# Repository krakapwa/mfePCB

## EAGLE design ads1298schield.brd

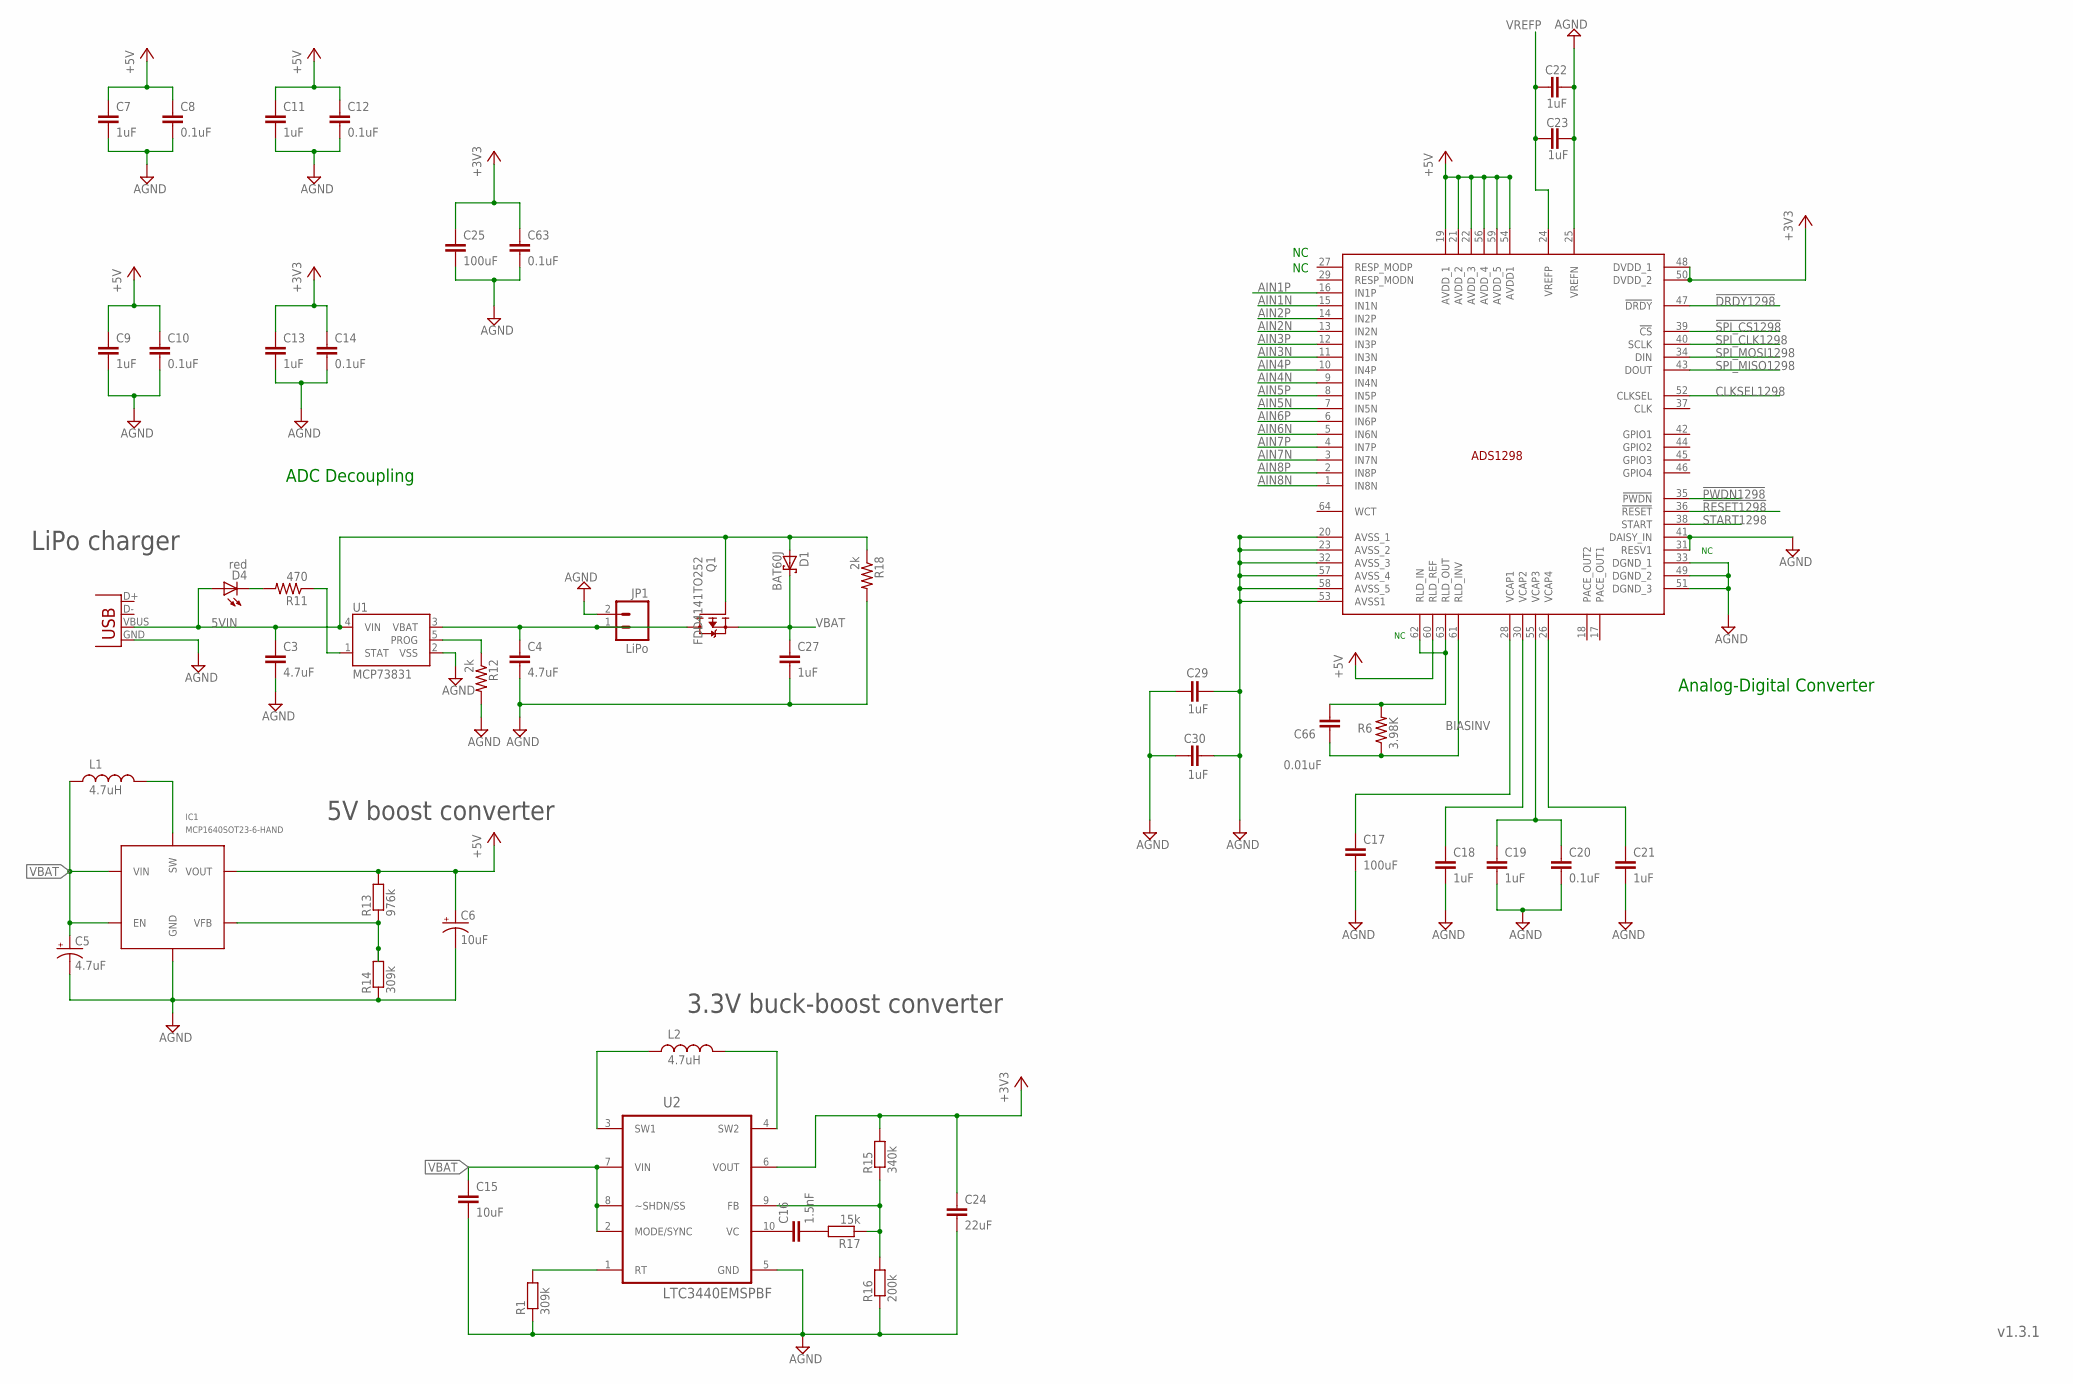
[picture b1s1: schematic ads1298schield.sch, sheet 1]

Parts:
C3, C4: 4.7uF; 0402-CAP
C5: 4.7uF; EIA3216
C6: 10uF; EIA3216
C7, C9, C11, C13, C18, C19, C21, C22, C23, C29, C30: 1uF; 0603-CAP
C8, C10, C12, C14, C20, C63: 0.1uF; 0603-CAP
C15: 10uF; 1210
C16: 1.5nF; 1210
C17, C25: 100uF; 1210
C24: 22uF; 1210
C27: 1uF; 0402-CAP
C66: 0.01uF; 0603-CAP
D1: BAT60J; SOD323_ST
D4: red; LED-0603
IC1: MCP1640SOT23-6-HAND; SOT23-6-HAND
JP1: LiPo; JST-2-SMD
L1, L2: 4.7uH; 1210-HAND
Q1: FDD4141TO252; TO252
R1, R14: 309k; 1206-HAND
R6: 3.98K; 0603-RES
R11: 470; 0402-RES
R12, R18: 2k; 0402-RES
R13: 976k; 1206-HAND
R15: 340k; 1206-HAND
R16: 200k; 1206-HAND
R17: 15k; 1206-HAND
U1: MCP73831; SOT23-5
U2: LTC3440EMSPBF; SOP50P490X110-10N
U$2: ADS1298*PAG*; TQFP64
X2: USB-MICROB

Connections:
5VIN: C3.1, D1.A, D4.A, Q1.1 (G), R18.1, U1.4 (VIN), X2.VBUS
!DRDY1298: U$2.47 (!DRDY); also elsewhere on the board
!PWDN1298: U$2.35 (!PWDN); also elsewhere on the board
!RESET1298: U$2.36 (!RESET); also elsewhere on the board
!SPI_CS1298: U$2.39 (!CS); also elsewhere on the board
+3V3: C13.1, C14.1, C24.1, C25.1, C63.1, R15.2, U2.6 (VOUT), U$2.48 (DVDD_1), U$2.50 (DVDD_2); also elsewhere on the board
+5V: C6.A (+), C7.1, C8.1, C9.1, C10.1, C11.1, C12.1, IC1.5 (VOUT), R13.2, U$2.19 (AVDD_1), U$2.21 (AVDD_2), U$2.22 (AVDD_3), U$2.54 (AVDD1), U$2.56 (AVDD_4), U$2.59 (AVDD_5), U$2.60 (RLD_REF); also elsewhere on the board
AGND: C3.2, C4.2, C5.C (-), C6.C (-), C7.2, C8.2, C9.2, C10.2, C11.2, C12.2, C13.2, C14.2, C15.2, C17.2, C18.2, C19.2, C20.2, C21.2, C22.2, C23.2, C24.2, C25.2, C27.2, C29.1, C29.2, C30.1, C30.2, C63.2, IC1.2 (GND), JP1.2, R1.1, R12.2, R14.1, R16.1, R18.2, U1.2 (VSS), U2.5 (GND), U$2.20 (AVSS_1), U$2.23 (AVSS_2), U$2.25 (VREFN), U$2.31 (RESV1), U$2.32 (AVSS_3), U$2.33 (DGND_1), U$2.41 (DAISY_IN), U$2.49 (DGND_2), U$2.51 (DGND_3), U$2.53 (AVSS1), U$2.57 (AVSS_4), U$2.58 (AVSS_5), X2.GND; also elsewhere on the board
AIN1N: U$2.15 (IN1N); also elsewhere on the board
AIN1P: U$2.16 (IN1P); also elsewhere on the board
AIN2N: U$2.13 (IN2N); also elsewhere on the board
AIN2P: U$2.14 (IN2P); also elsewhere on the board
AIN3N: U$2.11 (IN3N); also elsewhere on the board
AIN3P: U$2.12 (IN3P); also elsewhere on the board
AIN4N: U$2.9 (IN4N); also elsewhere on the board
AIN4P: U$2.10 (IN4P); also elsewhere on the board
AIN5N: U$2.7 (IN5N); also elsewhere on the board
AIN5P: U$2.8 (IN5P); also elsewhere on the board
AIN6N: U$2.5 (IN6N); also elsewhere on the board
AIN6P: U$2.6 (IN6P); also elsewhere on the board
AIN7N: U$2.3 (IN7N); also elsewhere on the board
AIN7P: U$2.4 (IN7P); also elsewhere on the board
AIN8N: U$2.1 (IN8N); also elsewhere on the board
AIN8P: U$2.2 (IN8P); also elsewhere on the board
BIASINV: C66.2, R6.1, U$2.61 (RLD_INV); also elsewhere on the board
CLKSEL1298: U$2.52 (CLKSEL); also elsewhere on the board
unnamed: C17.1, U$2.28 (VCAP1)
unnamed: C18.1, U$2.30 (VCAP2)
unnamed: C66.1, R6.2, U$2.62 (RLD_IN), U$2.63 (RLD_OUT)
unnamed: C21.1, U$2.26 (VCAP4)
unnamed: C19.1, C20.1, U$2.55 (VCAP3)
unnamed: R12.1, U1.5 (PROG)
unnamed: R11.1, U1.1 (STAT)
unnamed: R1.2, U2.1 (RT)
unnamed: D4.C, R11.2
unnamed: IC1.1 (SW), L1.2
unnamed: C5.A (+), IC1.3 (EN), IC1.6 (VIN), L1.1
unnamed: C16.1, U2.10 (VC)
unnamed: IC1.4 (VFB), R13.1, R14.2
unnamed: C15.1, U2.2 (MODE/SYNC), U2.7 (VIN), U2.8 (~SHDN/SS)
unnamed: L2.1, U2.3 (SW1)
unnamed: L2.2, U2.4 (SW2)
unnamed: R15.1, R16.2, R17.1, U2.9 (FB)
unnamed: C16.2, R17.2
SPI_CLK1298: U$2.40 (SCLK); also elsewhere on the board
SPI_MISO1298: U$2.43 (DOUT); also elsewhere on the board
SPI_MOSI1298: U$2.34 (DIN); also elsewhere on the board
START1298: U$2.38 (START); also elsewhere on the board
VBAT: C4.1, C27.1, D1.C, JP1.1, Q1.2 (S), Q1.3 (D), U1.3 (VBAT); also elsewhere on the board
VREFP: C22.1, C23.1, U$2.24 (VREFP)

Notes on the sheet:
v1.3.1
ADC Decoupling
Analog-Digital Converter
5V boost converter
LiPo charger
3.3V buck-boost converter

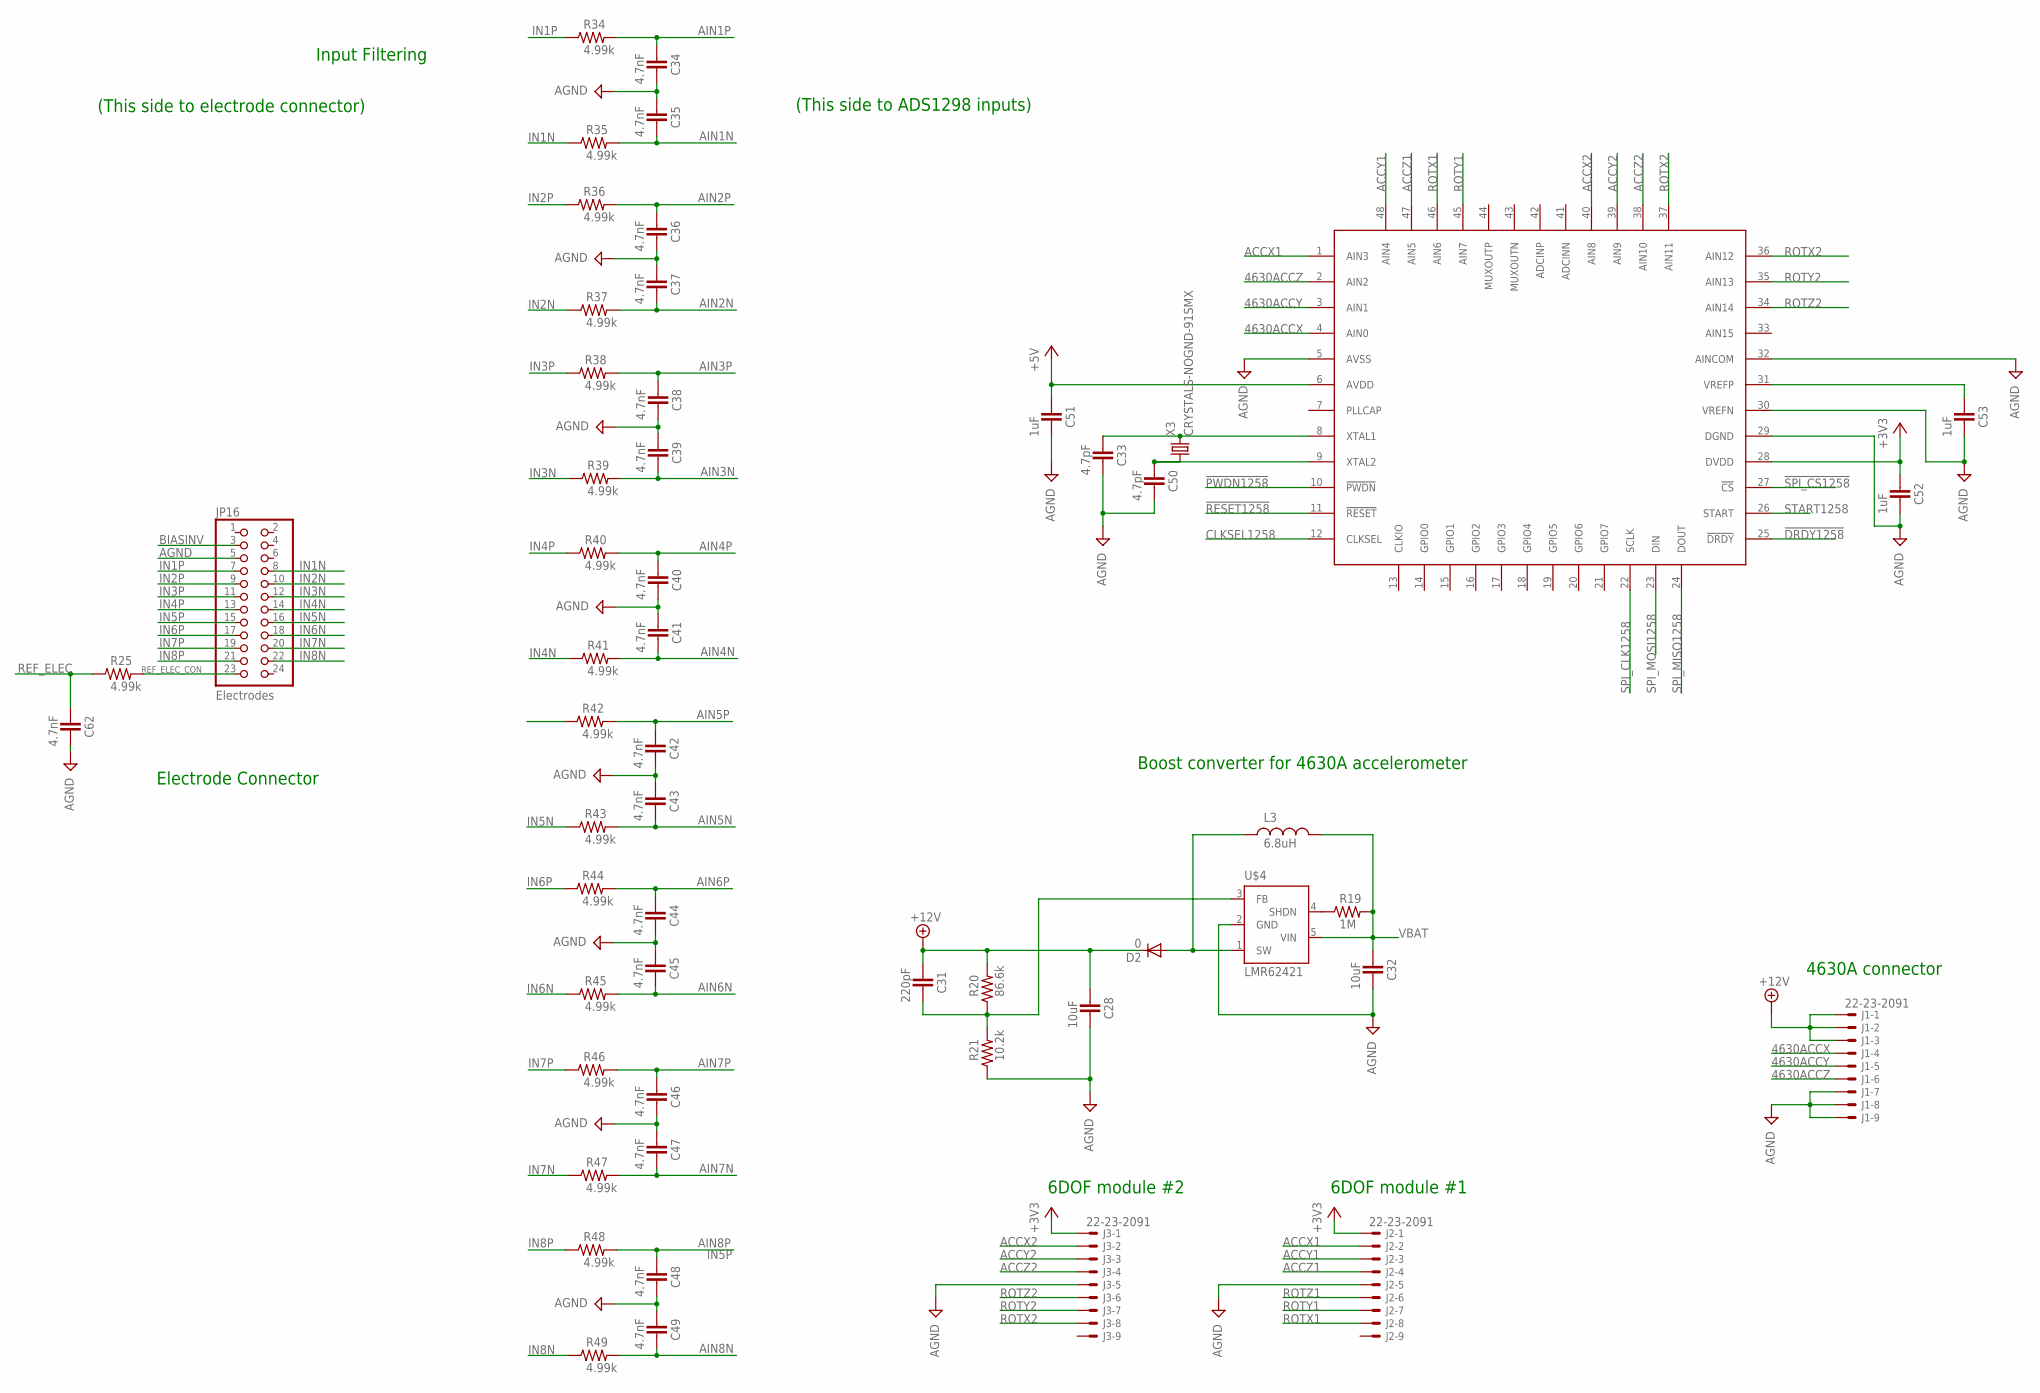
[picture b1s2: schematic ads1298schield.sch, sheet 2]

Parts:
C28, C32: 10uF; 0603-CAP
C31: 220pF; 0603-CAP
C33, C50: 4.7pF; 0603-CAP
C34, C35, C36, C37, C38, C39, C40, C41, C42, C43, C44, C45, C46, C47, C48, C49, C62: 4.7nF; 0603-CAP
C51, C52, C53: 1uF; 0603-CAP
D2: 0; MELF-MLL41
IC2: ADS1258; P-HVQFN48-7X7
J1, J2, J3: 22-23-2091
JP16: Electrodes; 2X12
L3: 6.8uH; 1210-HAND
R19: 1M; 0603-RES
R20: 86.6k; 0603-RES
R21: 10.2k; 0603-RES
R25, R34, R35, R36, R37, R38, R39, R40, R41, R42, R43, R44, R45, R46, R47, R48, R49: 4.99k; 0603-RES
U$4: LMR62421; SOT23-5
X3: CRYSTALS-NOGND-91SMX; 91SMX

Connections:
4630ACCX: IC2.4 (AIN0), J1.4
4630ACCY: IC2.3 (AIN1), J1.5
4630ACCZ: IC2.2 (AIN2), J1.6
!DRDY1258: IC2.25 (!DRDY); also elsewhere on the board
!PWDN1258: IC2.10 (!PWDN); also elsewhere on the board
!RESET1258: IC2.11 (!RESET); also elsewhere on the board
!SPI_CS1258: IC2.27 (!CS); also elsewhere on the board
+3V3: C52.1, IC2.28 (DVDD); also elsewhere on the board
+5V: C51.1, IC2.6 (AVDD); also elsewhere on the board
+12V: C28.1, C31.1, D2.C, J1.1, J1.2, J1.3, R20.2
AGND: C28.2, C32.2, C33.2, C34.2, C35.1, C36.2, C37.1, C38.2, C39.1, C40.2, C41.1, C42.2, C43.1, C44.2, C45.1, C46.2, C47.1, C48.2, C49.1, C50.2, C51.2, C52.2, C53.2, C62.2, IC2.5 (AVSS), IC2.29 (DGND), IC2.30 (VREFN), IC2.32 (AINCOM), J1.7, J1.8, J1.9, J2.5, J3.5, JP16.5, R21.1, U$4.2 (GND); also elsewhere on the board
AIN1N: C35.2, R35.2; also elsewhere on the board
AIN1P: C34.1, R34.2; also elsewhere on the board
AIN2N: C37.2, R37.2; also elsewhere on the board
AIN2P: C36.1, R36.2; also elsewhere on the board
AIN3N: C39.2, R39.2; also elsewhere on the board
AIN3P: C38.1, R38.2; also elsewhere on the board
AIN4N: C41.2, R41.2; also elsewhere on the board
AIN4P: C40.1, R40.2; also elsewhere on the board
AIN5N: C43.2, R43.2; also elsewhere on the board
AIN5P: C42.1, R42.2; also elsewhere on the board
AIN6N: C45.2, R45.2; also elsewhere on the board
AIN6P: C44.1, R44.2; also elsewhere on the board
AIN7N: C47.2, R47.2; also elsewhere on the board
AIN7P: C46.1, R46.2; also elsewhere on the board
AIN8N: C49.2, R49.2; also elsewhere on the board
AIN8P: C48.1, R48.2; also elsewhere on the board
BIASINV: JP16.3; also elsewhere on the board
CLKSEL1258: IC2.12 (CLKSEL); also elsewhere on the board
IN1N: JP16.8, R35.1
IN1P: JP16.7, R34.1
IN2N: JP16.10, R37.1
IN2P: JP16.9, R36.1
IN3N: JP16.12, R39.1
IN3P: JP16.11, R38.1
IN4N: JP16.14, R41.1
IN4P: JP16.13, R40.1
IN5N: JP16.16, R43.1
IN5P: JP16.15, R42.1
IN6N: JP16.18, R45.1
IN6P: JP16.17, R44.1
IN7N: JP16.20, R47.1
IN7P: JP16.19, R46.1
IN8N: JP16.22, R49.1
IN8P: JP16.21, R48.1
unnamed: R19.1, U$4.4 (SHDN)
unnamed: C33.1, IC2.8 (XTAL1), X3.2
unnamed: D2.A, L3.1, U$4.1 (SW)
unnamed: C50.1, IC2.9 (XTAL2), X3.1
unnamed: C31.2, R20.1, R21.2, U$4.3 (FB)
unnamed: C53.1, IC2.31 (VREFP)
unnamed: IC2.1 (AIN3), J2.2
unnamed: IC2.48 (AIN4), J2.3
unnamed: IC2.40 (AIN8), J3.2
unnamed: IC2.39 (AIN9), J3.3
unnamed: IC2.38 (AIN10), J3.4
unnamed: IC2.34 (AIN14), J3.6
unnamed: IC2.35 (AIN13), J3.7
unnamed: IC2.36 (AIN12), IC2.37 (AIN11), J3.8
REF_ELEC: C62.1, R25.1
REF_ELEC_CON: JP16.23, R25.2
SPI_CLK1258: IC2.22 (SCLK); also elsewhere on the board
SPI_MISO1258: IC2.24 (DOUT); also elsewhere on the board
SPI_MOSI1258: IC2.23 (DIN); also elsewhere on the board
START1258: IC2.26 (START); also elsewhere on the board
VBAT: C32.1, L3.2, R19.2, U$4.5 (VIN); also elsewhere on the board

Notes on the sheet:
Electrode Connector
Input Filtering
(This side to ADS1298 inputs)
(This side to electrode connector)
Boost converter for 4630A accelerometer
4630A connector
6DOF module #1
6DOF module #2

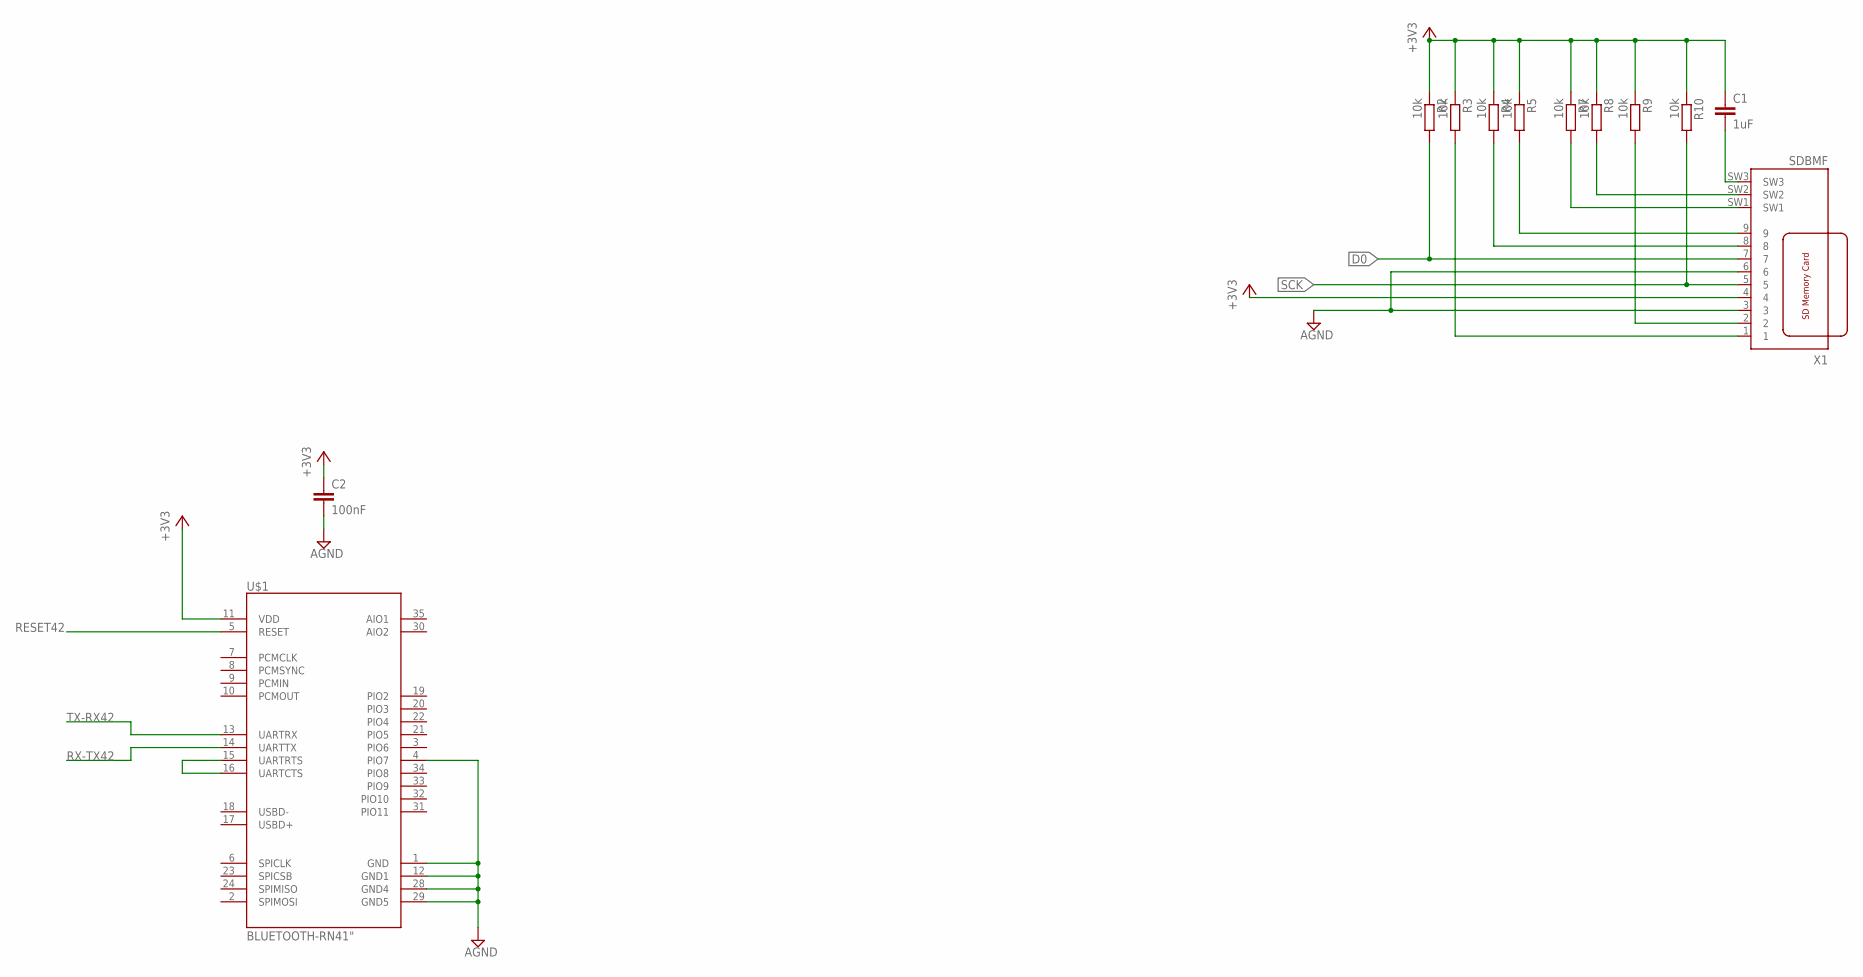
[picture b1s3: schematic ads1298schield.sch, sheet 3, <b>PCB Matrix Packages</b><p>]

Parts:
C1: 1uF; C1608
C2: 100nF; C0603
R2, R3, R4, R5, R7, R8, R9, R10: 10k; M1406
U$1: BLUETOOTH-RN41"; RN41
X1: SDBMF; SDBMF-009XXBXX2

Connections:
+3V3: C1.1, C2.1, R2.1, R3.1, R4.1, R5.1, R7.1, R8.1, R9.1, R10.1, U$1.11 (VDD), X1.4; also elsewhere on the board
AGND: C2.2, U$1.1 (GND), U$1.4 (PIO7), U$1.12 (GND1), U$1.28 (GND4), U$1.29 (GND5), X1.3, X1.6; also elsewhere on the board
CMD: R9.2, X1.2
D0: R2.2, X1.7
LINK: U$1.15 (UARTRTS), U$1.16 (UARTCTS)
unnamed: R3.2, X1.1
unnamed: R4.2, X1.8
unnamed: R5.2, X1.9
unnamed: R7.2, X1.SW1
unnamed: R8.2, X1.SW2
unnamed: C1.2, X1.SW3
RESET42: U$1.5 (RESET); also elsewhere on the board
RX-TX42: U$1.14 (UARTTX); also elsewhere on the board
SCK: R10.2, X1.5
TX-RX42: U$1.13 (UARTRX); also elsewhere on the board

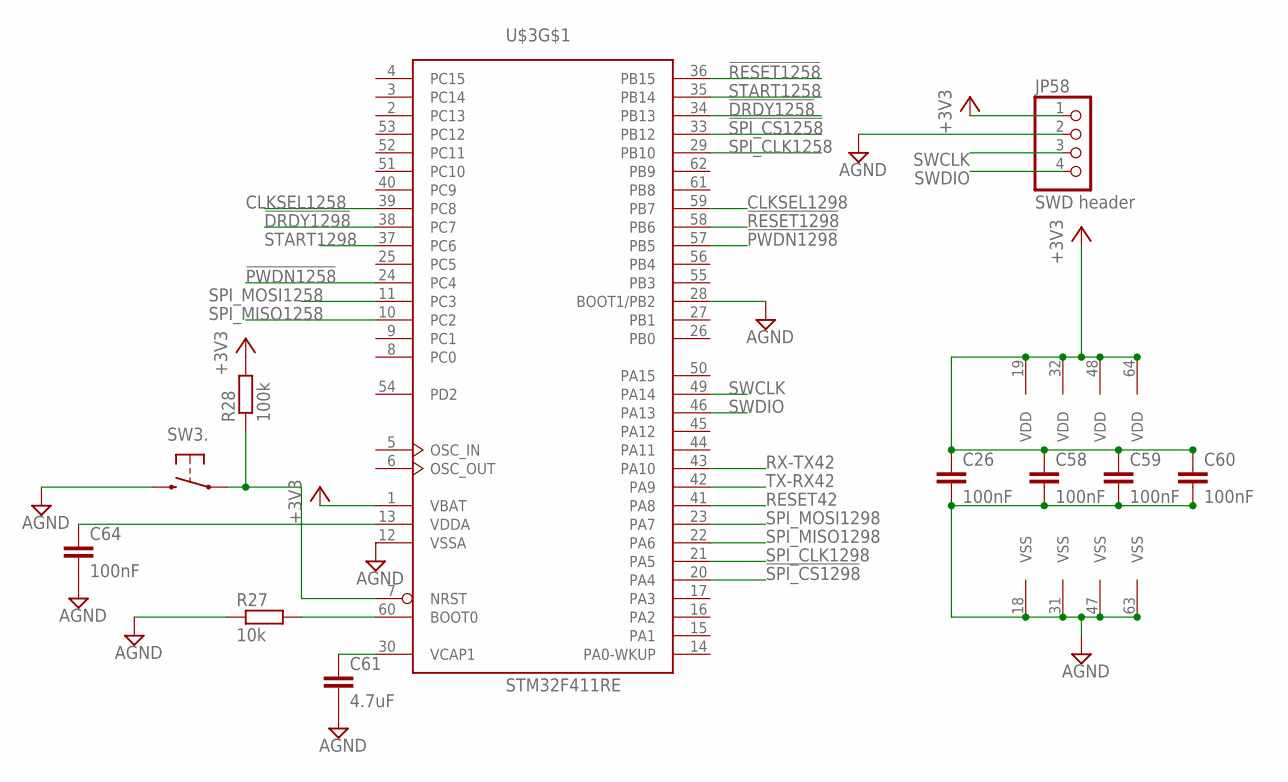
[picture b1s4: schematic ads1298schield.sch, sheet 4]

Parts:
C26, C58, C59, C60, C64: 100nF; C1210
C61: 4.7uF; C1210
JP58: SWD header; 1X04
R27: 10k; M1406
R28: 100k; M1406
SW3: !RST; SWITCH-TACT-B3U-1100P-B
U$3: STM32F411RE; LQFP64

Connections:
!DRDY1258: U$3.34 (PB13); also elsewhere on the board
!DRDY1298: U$3.38 (PC7); also elsewhere on the board
!PWDN1258: U$3.24 (PC4); also elsewhere on the board
!PWDN1298: U$3.57 (PB5); also elsewhere on the board
!RESET1258: U$3.36 (PB15); also elsewhere on the board
!RESET1298: U$3.58 (PB6); also elsewhere on the board
!SPI_CS1258: U$3.33 (PB12); also elsewhere on the board
!SPI_CS1298: U$3.20 (PA4); also elsewhere on the board
+3V3: C26.1, C58.1, C59.1, C60.1, JP58.1, R28.2, U$3.1 (VBAT), U$3.19 (VDD), U$3.32 (VDD), U$3.48 (VDD), U$3.64 (VDD); also elsewhere on the board
AGND: C26.2, C58.2, C59.2, C60.2, C61.2, C64.2, JP58.2, R27.1, SW3.2, U$3.12 (VSSA), U$3.18 (VSS), U$3.28 (BOOT1/PB2), U$3.31 (VSS), U$3.47 (VSS), U$3.63 (VSS); also elsewhere on the board
CLKSEL1258: U$3.39 (PC8); also elsewhere on the board
CLKSEL1298: U$3.59 (PB7); also elsewhere on the board
unnamed: C61.1, U$3.30 (VCAP1)
unnamed: R27.2, U$3.60 (BOOT0)
unnamed: C64.1, U$3.13 (VDDA)
unnamed: R28.1, SW3.1, U$3.7 (NRST)
RESET42: U$3.41 (PA8); also elsewhere on the board
RX-TX42: U$3.43 (PA10); also elsewhere on the board
SPI_CLK1258: U$3.29 (PB10); also elsewhere on the board
SPI_CLK1298: U$3.21 (PA5); also elsewhere on the board
SPI_MISO1258: U$3.10 (PC2); also elsewhere on the board
SPI_MISO1298: U$3.22 (PA6); also elsewhere on the board
SPI_MOSI1258: U$3.11 (PC3); also elsewhere on the board
SPI_MOSI1298: U$3.23 (PA7); also elsewhere on the board
START1258: U$3.35 (PB14); also elsewhere on the board
START1298: U$3.37 (PC6); also elsewhere on the board
SWCLK: JP58.3, U$3.49 (PA14)
SWDIO: JP58.4, U$3.46 (PA13)
TX-RX42: U$3.42 (PA9); also elsewhere on the board

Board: 2 copper layers, 124 parts (0 on the bottom side), 106 nets, no tracks yet.

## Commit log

2015-11-13 v0.1
2015-11-15 v0.12
2015-11-16 v0.3
2015-11-20 v0.4

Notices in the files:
parts and their libraries:
SparkFun-Passives: Licensing: CC v3.0 Share-Alike You are welcome to use this library for commercial purposes.
